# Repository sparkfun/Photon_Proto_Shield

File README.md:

# Photon_Shield_Template
Template layout and Eagle library for Photon Shields

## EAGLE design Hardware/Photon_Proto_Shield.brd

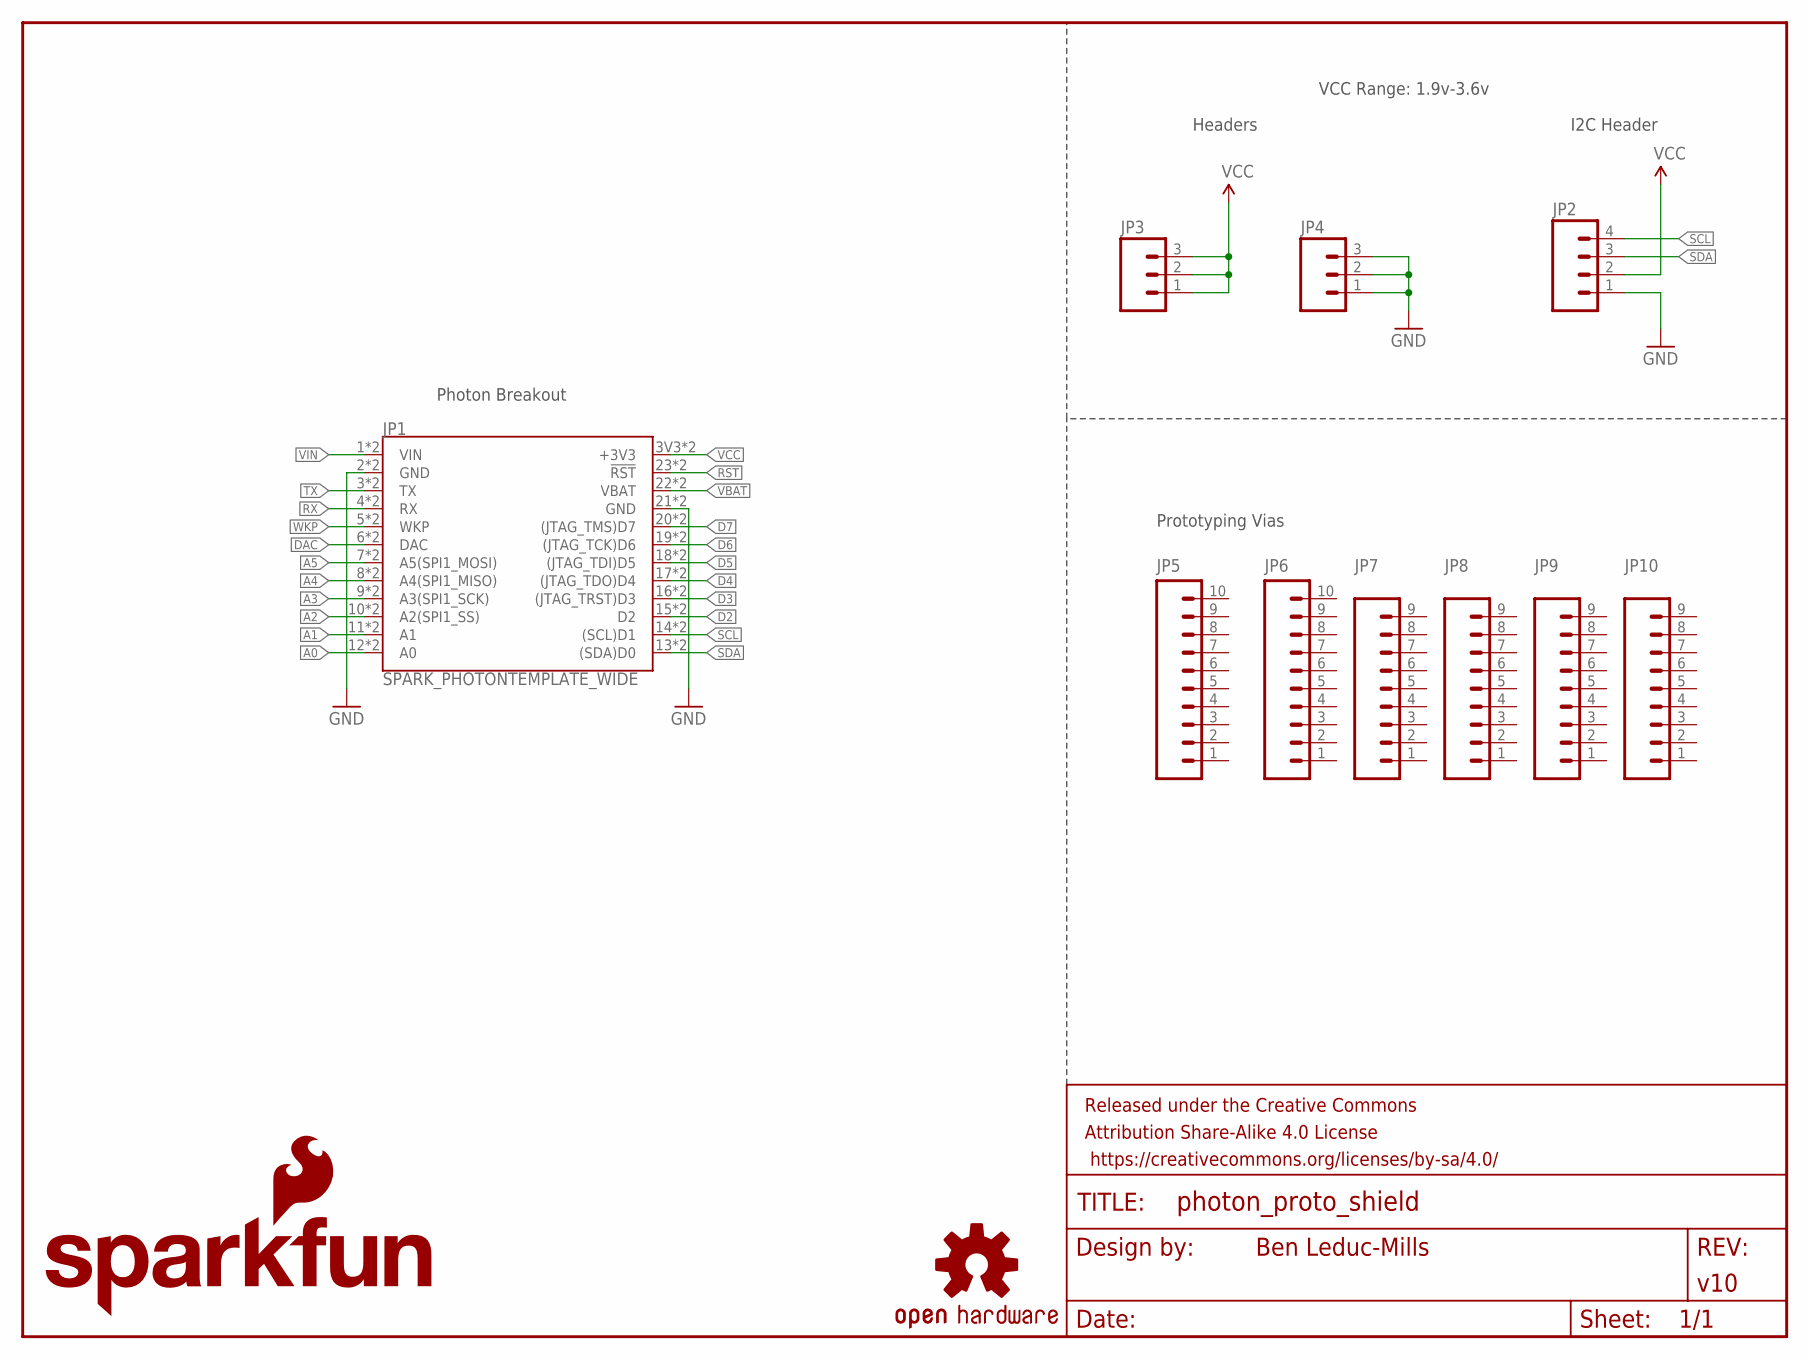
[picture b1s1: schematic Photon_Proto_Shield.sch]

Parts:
FRAME1: FRAME-LETTER; CREATIVE_COMMONS
JP1: SPARK_PHOTONTEMPLATE_WIDE; SPARK_PHOTON_TEMPLATE_WIDE
JP2: M04PTH; 1X04
JP3, JP4: M03PTH; 1X03
JP5, JP6: M10NO_SILK_PTH_FEMALE; 1X10_NO_SILK
JP7, JP8, JP9, JP10: M09NO_SILK; 1X09_NO_SILK
LOGO1: SFE_LOGO_NAME_FLAME.1_INCH; SFE_LOGO_NAME_FLAME_.1
LOGO2: OSHW-LOGOS; OSHW-LOGO-S

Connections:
A0: JP1.12 (A0), JP1.A0
A1: JP1.11 (A1), JP1.A1
A2: JP1.10 (A2(SPI1_SS)), JP1.A2 (A2(SPI1_SS))
A3: JP1.9 (A3(SPI1_SCK)), JP1.A3 (A3(SPI1_SCK))
A4: JP1.8 (A4(SPI1_MISO)), JP1.A4 (A4(SPI1_MISO))
A5: JP1.7 (A5(SPI1_MOSI)), JP1.A5 (A5(SPI1_MOSI))
D2: JP1.15 (D2), JP1.D2
D3: JP1.16 ((JTAG_TRST)D3), JP1.D3 ((JTAG_TRST)D3)
D4: JP1.17 ((JTAG_TDO)D4), JP1.D4 ((JTAG_TDO)D4)
D5: JP1.18 ((JTAG_TDI)D5), JP1.D5 ((JTAG_TDI)D5)
D6: JP1.19 ((JTAG_TCK)D6), JP1.D6 ((JTAG_TCK)D6)
D7: JP1.20 ((JTAG_TMS)D7), JP1.D7 ((JTAG_TMS)D7)
DAC: JP1.6 (DAC), JP1.DAC
GND: JP1.2 (GND), JP1.21 (GND), JP1.GND@0 (GND), JP1.GND@2 (GND), JP2.1, JP4.1, JP4.2, JP4.3
RST: JP1.23 (!RST!), JP1.RST (!RST!)
RX: JP1.4 (RX), JP1.RX
SCL: JP1.14 ((SCL)D1), JP1.D1 ((SCL)D1), JP2.4
SDA: JP1.13 ((SDA)D0), JP1.D0 ((SDA)D0), JP2.3
TX: JP1.3 (TX), JP1.TX
VBAT: JP1.22 (VBAT), JP1.VBAT
VCC: JP1.3V3 (+3V3), JP1.24 (+3V3), JP2.2, JP3.1, JP3.2, JP3.3
VIN: JP1.1 (VIN), JP1.VIN
WKP: JP1.5 (WKP), JP1.WKP

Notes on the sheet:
I2C Header
Prototyping Vias
Headers
Photon Breakout
VCC Range: 1.9v-3.6v

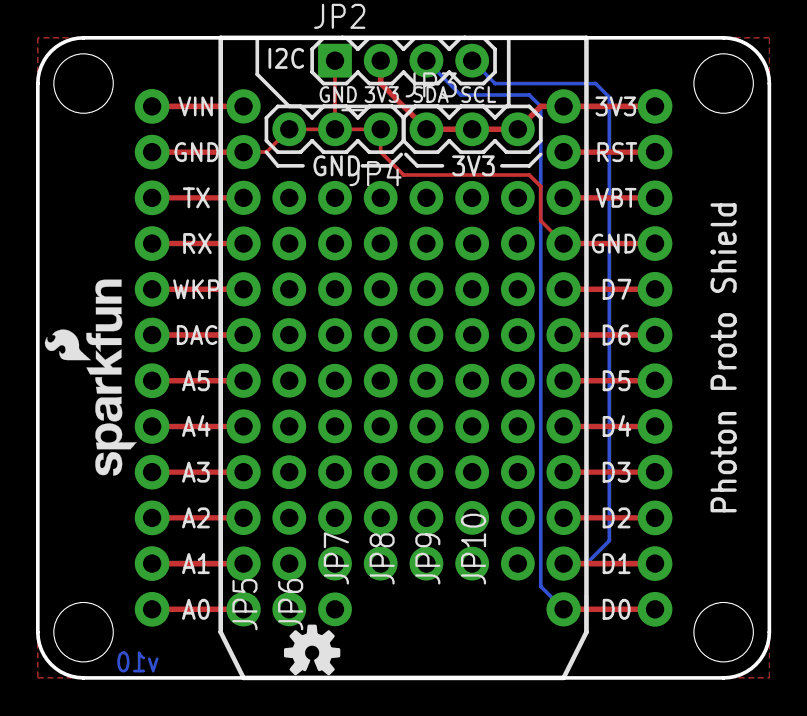
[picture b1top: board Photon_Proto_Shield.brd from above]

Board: 2 copper layers, 40.6 x 35.6 mm, 14 parts (1 on the bottom side), 23 nets.

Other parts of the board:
LOGO3: SFE_LOGO_NAME_FLAME.1_INCH; SFE_LOGO_NAME_FLAME_.1

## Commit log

2015-03-04 Initial upload
2015-03-04 Fixed top dimension layer
    Resolved issue #1
2015-04-01 update
    changed name on silk
2015-05-11 Adding gap between Photon and pin breakouts.
2015-05-11 Revising file structure to match standard.
2015-05-11 Changed per design review
    Box around I2C breakout, moved sad and scale traces outside of photo
    area, cleaned up silk on gnd and 3v3 busses.
2015-05-11 changed name
    per new naming conventions
2015-05-22 Bottom-lefting origin. Revising board name.
2015-05-22 Updating silk. Re-routing ground plane.
2015-05-27 Change VCC from flag label to VCC symbol
2015-09-03 Adding license, updating README

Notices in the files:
parts and their libraries:
SparkFun-Aesthetics: Licensing: Creative Commons ShareAlike 4.0 International - https://creativecommons.org/licenses/by-sa/4.0
SparkFun-Aesthetics: Released under the Creative Commons Attribution Share-Alike 4.0 License
SparkFun-Aesthetics: https://creativecommons.org/licenses/by-sa/4.0
